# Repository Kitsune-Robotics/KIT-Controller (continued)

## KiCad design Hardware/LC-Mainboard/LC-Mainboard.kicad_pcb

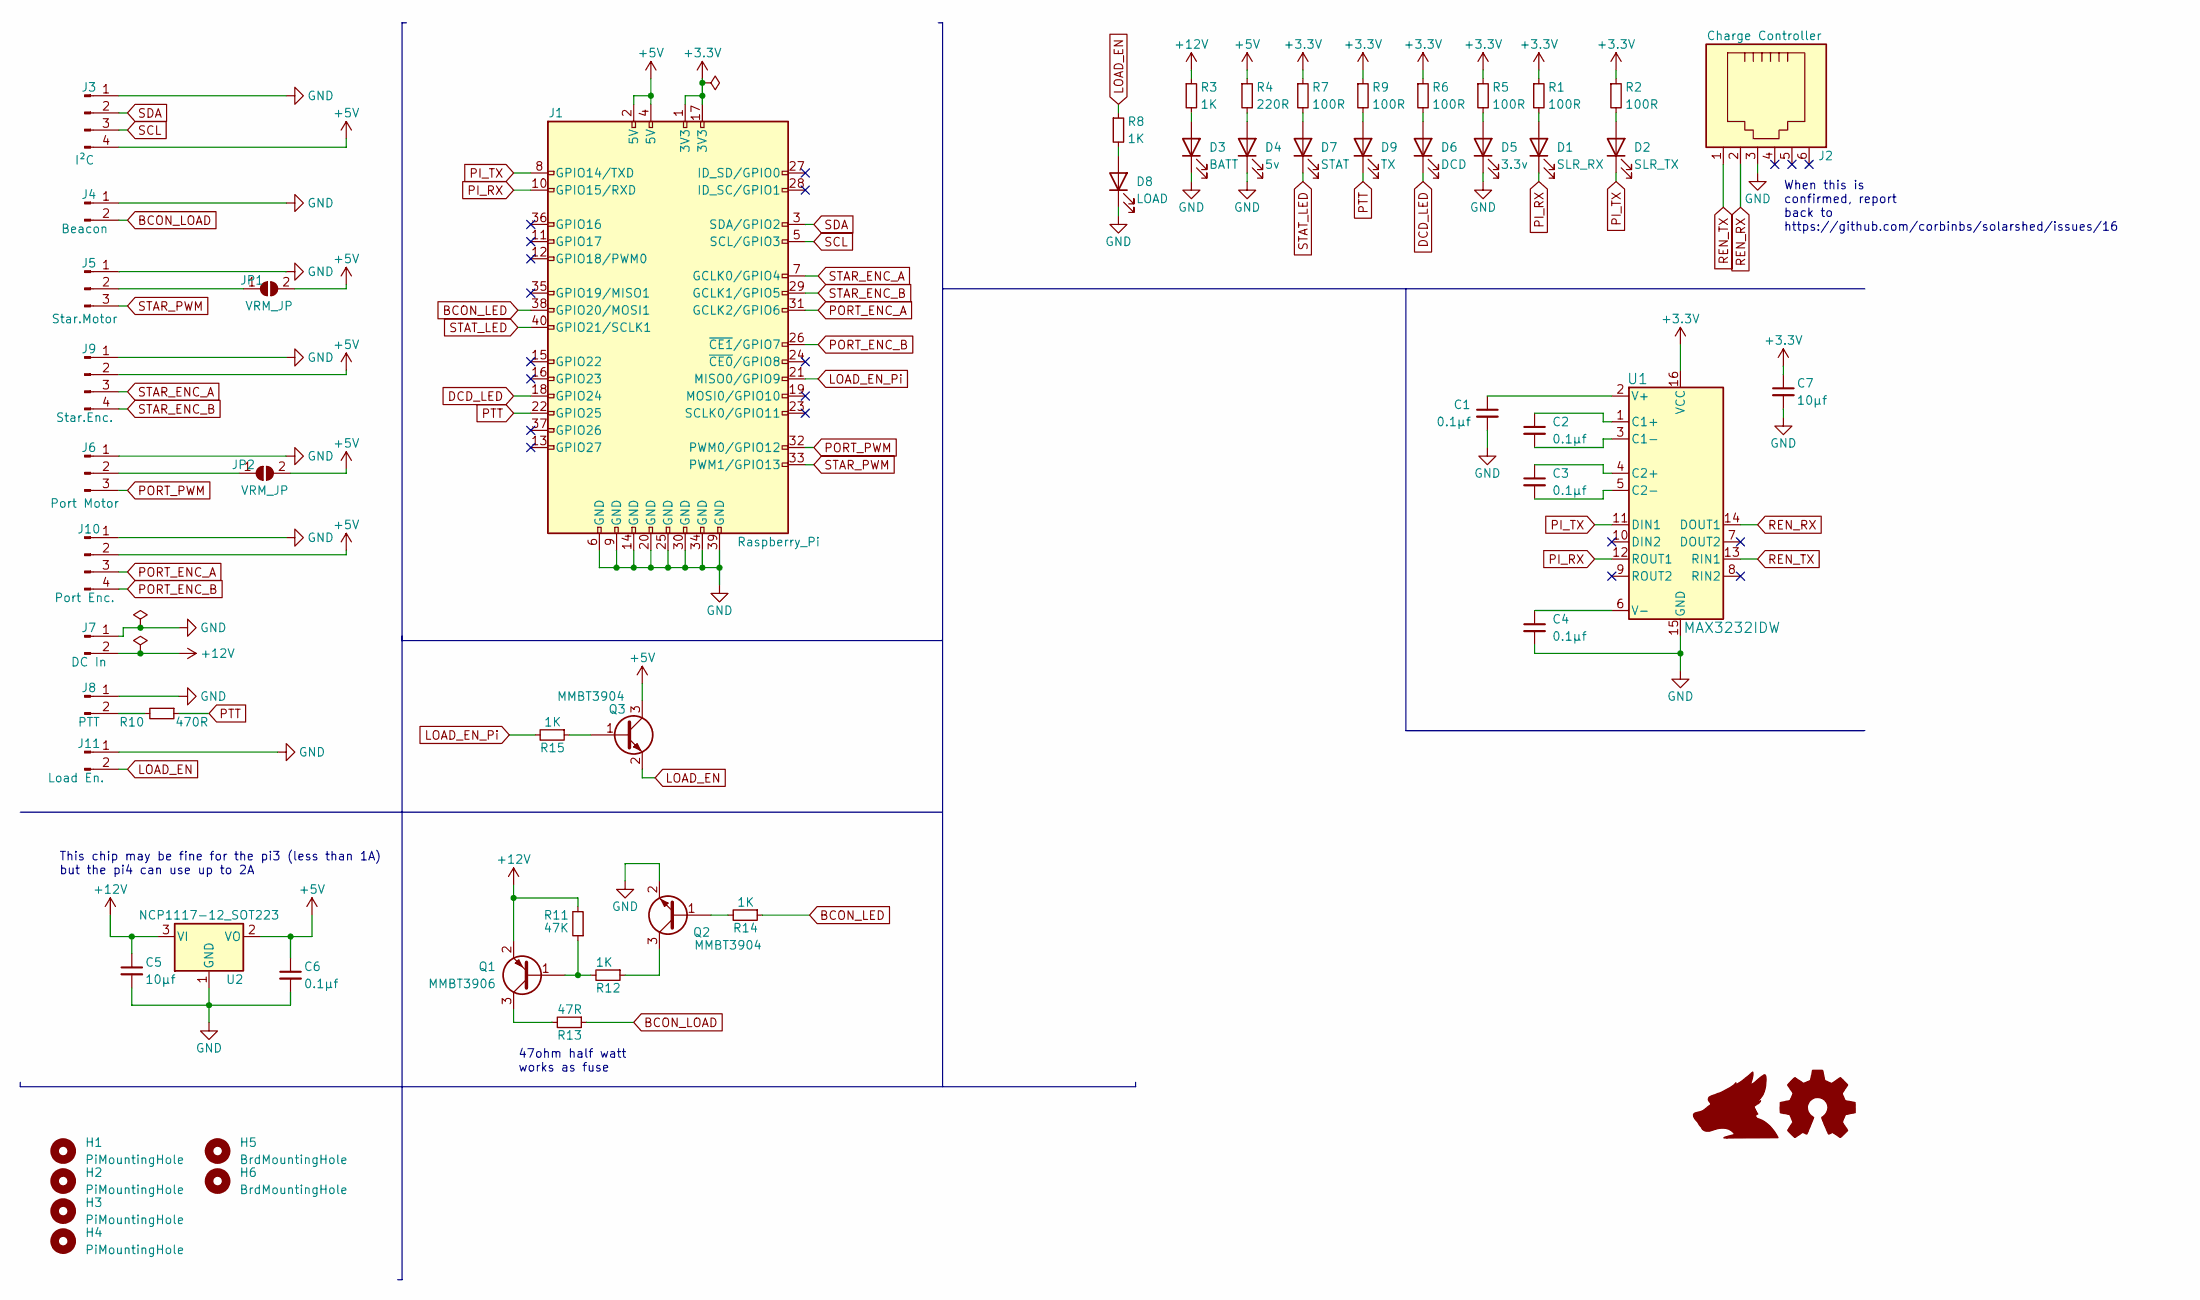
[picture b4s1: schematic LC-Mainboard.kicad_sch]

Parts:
C1, C2, C3, C4, C6: 0.1μf; C_0805_2012Metric
C5, C7: 10μf; C_Elec_4x5.4
D1: SLR_RX; LED_0805_2012Metric
D2: SLR_TX; LED_0805_2012Metric
D3: BATT; LED_0805_2012Metric
D4: 5v; LED_0805_2012Metric
D5: 3.3v; LED_0805_2012Metric
D6: DCD; LED_0805_2012Metric
D7: STAT; LED_0805_2012Metric
D8: LOAD; LED_0805_2012Metric
D9: TX; LED_0805_2012Metric
H1, H2, H3, H4: PiMountingHole; MountingHole_3mm
H5, H6: BrdMountingHole; MountingHole_3mm
J1: Raspberry_Pi; PinSocket_2x20_P2.54mm_Vertical
J2: Charge Controller; RJ12_Amphenol_54601
J3: I²C; JST_XH_S4B-XH-A_1x04_P2.50mm_Horizontal
J4: Beacon; JST_XH_S2B-XH-A_1x02_P2.50mm_Horizontal
J5: Star.Motor; JST_XH_S3B-XH-A_1x03_P2.50mm_Horizontal
J6: Port Motor; JST_XH_S3B-XH-A_1x03_P2.50mm_Horizontal
J7: DC In; JST_XH_S2B-XH-A_1x02_P2.50mm_Horizontal
J8: PTT; JST_XH_S2B-XH-A_1x02_P2.50mm_Horizontal
J9: Star.Enc.; JST_XH_S4B-XH-A_1x04_P2.50mm_Horizontal
J10: Port Enc.; JST_XH_S4B-XH-A_1x04_P2.50mm_Horizontal
J11: Load En.; JST_XH_S2B-XH-A_1x02_P2.50mm_Horizontal
JP1, JP2: VRM_JP; SolderJumper-2_P1.3mm_Open_Pad1.0x1.5mm
Q1: MMBT3906; SOT-23
Q2, Q3: MMBT3904; SOT-23
R1, R2, R5, R6, R7, R9: 100R; R_0805_2012Metric
R3, R8, R12, R14, R15: 1K; R_0805_2012Metric
R4: 220R; R_0805_2012Metric
R10: 470R; R_0805_2012Metric
R11: 47K; R_0805_2012Metric
R13: 47R; R_0805_2012Metric
U1: MAX3232IDW
U2: NCP1117-12_SOT223; SOT-223-3_TabPin2

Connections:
+3V3: C7.1, J1.1 (3V3), J1.17 (3V3), R1.1, R2.1, R5.1, R6.1, R7.1, R9.1, U1.16 (VCC)
+5V: C6.1, J1.2 (5V), J1.4 (5V), J3.4, J9.2, J10.2, JP1.2 (B), JP2.2 (B), Q3.3 (C), R4.1, U2.2 (VO)
+12V: C5.1, J7.2, Q1.2 (E), R3.1, R11.2, U2.3 (VI)
BCON_LED: J1.38 (GPIO20/MOSI1), R14.1
BCON_LOAD: J4.2, R13.1
DCD_LED: D6.1 (K), J1.18 (GPIO24)
GND: C1.2, C4.2, C5.2, C6.2, C7.2, D3.1 (K), D4.1 (K), D5.1 (K), D8.1 (K), J1.6 (GND), J1.9 (GND), J1.14 (GND), J1.20 (GND), J1.25 (GND), J1.30 (GND), J1.34 (GND), J1.39 (GND), J2.3, J3.1, J4.1, J5.1, J6.1, J7.1, J8.1, J9.1, J10.1, J11.1, Q2.2 (E), U1.15 (GND), U2.1 (GND)
LOAD_EN: J11.2, Q3.2 (E), R8.1
LOAD_EN_Pi: J1.21 (MISO0/GPIO9), R15.2
unnamed: C1.1, U1.2 (V+)
unnamed: C2.1, U1.1 (C1+)
unnamed: C2.2, U1.3 (C1-)
unnamed: C3.1, U1.4 (C2+)
unnamed: C3.2, U1.5 (C2-)
unnamed: C4.1, U1.6 (V-)
unnamed: D1.2 (A), R1.2
unnamed: D2.2 (A), R2.2
unnamed: D3.2 (A), R3.2
unnamed: D4.2 (A), R4.2
unnamed: D5.2 (A), R5.2
unnamed: D6.2 (A), R6.2
unnamed: D7.2 (A), R7.2
unnamed: D8.2 (A), R8.2
unnamed: D9.2 (A), R9.2
unnamed: J5.2, JP1.1 (A)
unnamed: J6.2, JP2.1 (A)
unnamed: J8.2, R10.2
unnamed: Q1.1 (B), R11.1, R12.2
unnamed: Q1.3 (C), R13.2
unnamed: Q2.1 (B), R14.2
unnamed: Q2.3 (C), R12.1
unnamed: Q3.1 (B), R15.1
PI_RX: D1.1 (K), J1.10 (GPIO15/RXD), U1.12 (ROUT1)
PI_TX: D2.1 (K), J1.8 (GPIO14/TXD), U1.11 (DIN1)
PORT_ENC_A: J1.31 (GCLK2/GPIO6), J10.3
PORT_ENC_B: J1.26 (~CE1/GPIO7), J10.4
PORT_PWM: J1.32 (PWM0/GPIO12), J6.3
PTT: D9.1 (K), J1.22 (GPIO25), R10.1
REN_RX: J2.2, U1.14 (DOUT1)
REN_TX: J2.1, U1.13 (RIN1)
SCL: J1.5 (SCL/GPIO3), J3.3
SDA: J1.3 (SDA/GPIO2), J3.2
STAR_ENC_A: J1.7 (GCLK0/GPIO4), J9.3
STAR_ENC_B: J1.29 (GCLK1/GPIO5), J9.4
STAR_PWM: J1.33 (PWM1/GPIO13), J5.3
STAT_LED: D7.1 (K), J1.40 (GPIO21/SCLK1)

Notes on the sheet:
When this is confirmed, report back to https://github.com/corbinbs/solarshed/issues/16
47ohm half watt works as fuse
This chip may be fine for the pi3 (less than 1A) but the pi4 can use up to 2A

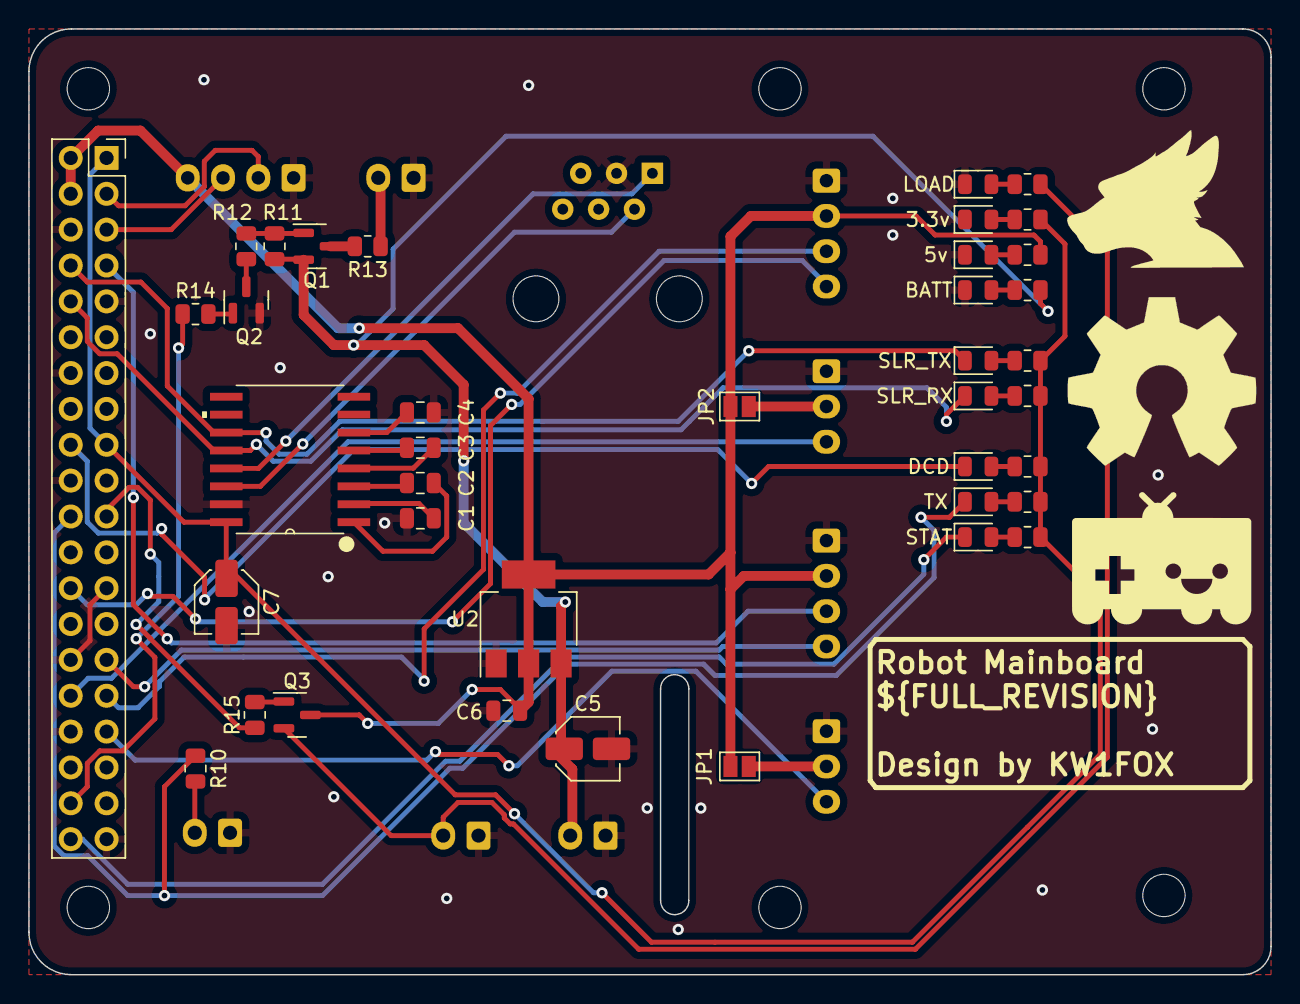
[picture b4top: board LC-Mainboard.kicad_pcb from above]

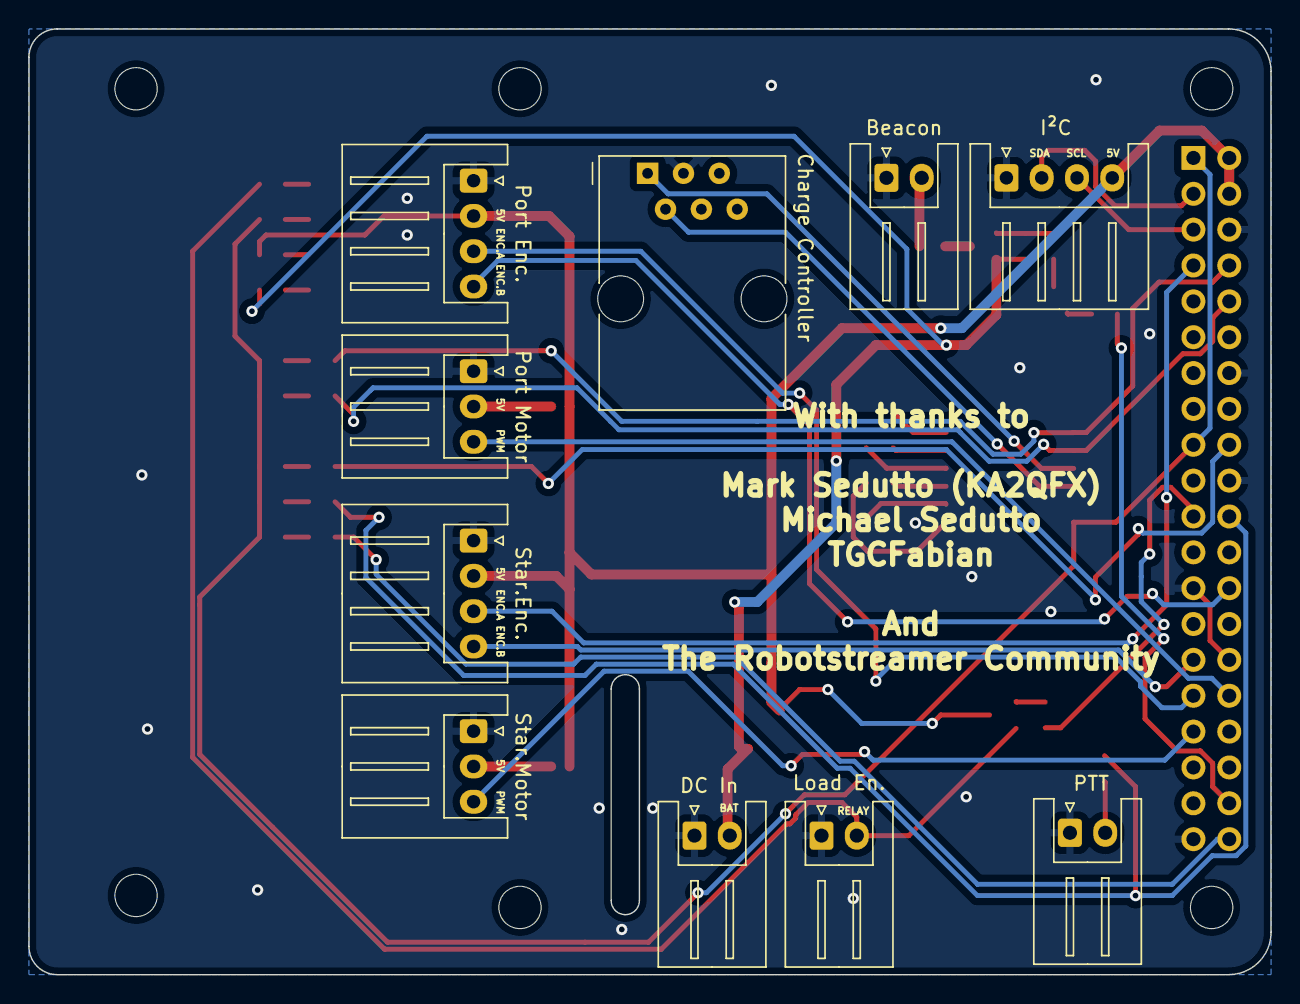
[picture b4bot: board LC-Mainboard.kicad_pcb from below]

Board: 2 copper layers, 88.0 x 67.0 mm, 55 parts (10 on the bottom side), 46 nets.

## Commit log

2022-04-12 import from feat/motor_mounts
2022-04-22 Bump CAD
2022-04-28 move everything
2022-04-28 Fixup new everything
2022-04-28 make encoder holder
2022-04-28 Clean encoder holder
2022-04-29 Fixup cad and assy
2022-04-29 Boilerplate PCB sketch
2022-04-29 Add lib depend, remove bak and boilerplate
2022-04-29 Update all
2022-04-29 Fix encoder spacer, bump lib and implement max3232 in sch
2022-04-29 Bump
2022-04-29 Init to commit it
2022-04-29 fixup! Init to commit it
2022-04-29 Bump logo
2022-04-29 Add designators
2022-04-30 bump lib and add LEDs
2022-04-30 Add a bunch of stuff
2022-04-30 Crawler Hardware (#1)
    This boilerplates all the hardware, a new branch should be made for producing a v0.1
2022-04-30 Switch to the correct connectors
2022-05-01 Do a little math
    Co-Authored by: Libidja
2022-05-01 Rearrange holes
2022-05-01 fixup! Rearrange holes
2022-05-03 Most of the routing is patched up, review with dad!
2022-05-03 Shrink board size
2022-05-03 Shrink board size even more!
2022-05-03 Add all wiring
2022-05-04 Add almost everything
2022-05-04 Add some extra things
2022-05-04 Fix 3d model
2022-05-04 Ready for review
2022-05-04 Add silkscreen
2022-05-04 Review from @ka2qfx went well!
2022-05-04 fixup! Review from @ka2qfx went well!
2022-05-04 Add last touches and fix all DRC
2022-05-04 fixup! Add last touches and fix all DRC
2022-05-04 Change direction, pi can now control load control
2022-05-04 Its done, all systems checked and final
2022-05-04 Make a v1.0 hardware release (#2)
2022-05-04 Add blank text variabes
2022-05-04 Add blank text variabes (#3)
    Seems to work fine and dosent interfere with text replacmeent in ci, merging.
2022-05-05 Update master assy
2022-05-05 Import v0.1 mainboard
2022-05-05 Only run on hardware paths
2022-05-09 Bump kicad libs
2022-05-19 Bump kicad
2022-05-19 Create inital Mastcam base
2022-05-19 Experiment with a new encoder base
    Suggestions by @ka2qfx
2022-05-19 Cleanup
2022-05-19 Fix bug rebuilding hardware on pull request
2022-05-19 resize encoder base
2022-05-19 Redesign mastcam base
2022-05-19 Add weighted wiper and 9g servo
2022-05-20 Fixup encoder and mastcam base
2022-05-21 Issue with smbus, fix l8r goodnight
2022-05-21 Move rospackages to the right location
2022-05-21 Create working inital LCD subscriber
2022-05-21 Halfway to a new package
2022-05-21 Got this working
2022-05-21 Add publisher
2022-05-21 Boilerplate pubsub
2022-05-21 Redo tutorial package live on stream
2022-05-21 Dont build on nothing
2022-05-21 Create a launchfile
2022-05-21 Add launch to make
2022-05-22 Cleanup names and add ros_workflow
2022-05-22 Fixup black formatting errors
2022-05-22 Update hardware_workflow.yml
    Fix a bug where workflow builds all the time evern when not needed
2022-05-22 Clean custom interfaces
2022-05-22 Custom message types!
2022-05-22 Handle multiple stats and cycle through them
2022-05-22 Add ci for ros2 lcd_viewer package
2022-05-22 Tests are dumb anyway
2022-05-22 Add all new mast parts
2022-05-22 Replace old mast parts with new ones
2022-05-22 Add new fancy feature EXPERIMENTAL
2022-05-23 Add small lip around base of camera pod drive gear
2022-05-23 Fix hole size on gearbox mounting plate
2022-05-23 Increase motor mounting bearing tolerence
2022-05-23 All done for the day
2022-05-23 Modify stuff idk i cant keep track of binary diffs
2022-05-23 Add top of box
2022-05-23 Clean up mastpod top
2022-05-24 Add camera housing base
2022-05-25 Add bottom mounting and sealing to pod housing
2022-05-25 Add mast pod base inital
2022-05-25 Add base to model
2022-05-25 Add more mounting holes and fluff
2022-05-25 More done to the top half
2022-05-25 Add limit switch
2022-05-26 Add sensors to mastcam base
2022-05-26 Create jig for solder mask
2022-05-26 Add cm4 template
2022-05-26 Add footprints too
2022-05-27 Add nokia libs
2022-05-27 Add encoder to drive gear
2022-05-27 Revert MastPodTop
2022-05-27 Extend pod height for potentometer
2022-05-27 Integrate encoder back into design
2022-05-27 Create glass and shell, more work needed
2022-05-27 Hide datum
2022-05-28 Improve fit
2022-06-09 Firmware doots
2022-06-09 Fix bug where PR would bypass checking if hardware needed to be built
2022-06-09 Create firmware workflow
2022-06-09 fixup! Create firmware workflow
2022-06-09 Change artifacts name
2022-06-09 Add cutout for 10 turn pot
2022-06-10 Fix serial debugging issue, thanks to Jck_true on IRC
2022-06-23 Replace caps with the right sized ones
2022-06-27 This doesent work
2022-06-30 Idk firmware
2022-10-01 clean modules
2022-10-02 bump lib with new backplane shared
2022-12-07 Inital migration of new kicad board
2022-12-07 Misc cleanup in .pro
2022-12-07 Satisfy constraints
2022-12-07 fixup! Satisfy constraints
2022-12-07 Fixup fixups and fixup the fixups
2022-12-08 Cleanup external libs and add extra bits to brd
2022-12-08 Pad more components
2022-12-08 Move MCU to its own schem
2022-12-08 add other junk idk
2022-12-08 Add more stuff
2022-12-08 Fixup drc
2022-12-10 Add short range modem
2022-12-20 Add TM1000 Tip over sensor and updates from custom lib
2022-12-20 Add clearance cutput in gearbox-mount
2023-02-08 Add inital glass
2023-07-10 bump all
2023-07-10 bump libs and squeeze into shape
2023-07-11 Add gnd and cleanup
2023-07-11 Add SD cardg
2023-07-13 include upstream fixes in kit controller
2023-10-23 Add stuff
2023-10-23 Not exactly the direction i want but, its a start
2023-10-23 Bump to new ver
2023-10-24 Remove software
2023-10-24 Add new pico firmware, depend on wizo libs
2023-10-24 Consider build flags later
2023-11-27 Add default freertosconfig
2023-11-27 Add default vfs config
2023-11-27 Add example includes from https://github.com/maxgerhardt/wizio-pico/blob/main/examples/picosdk-littlefs-freertos/src/main.cpp
2023-11-27 Add readme
2024-01-17 Add new base for future pieces
2024-01-22 Move CAD, make new sheet metal bend
2024-02-02 really want to print this
2024-04-02 Bump to kicad8
2024-04-02 Bump to kicad8 (again)
2024-04-02 Remove all CAD
2024-04-02 Remove simulation
2024-04-02 Clean all
2024-04-02 Everything New (#8)
2024-04-03 Import backplane from fennec modem
2024-04-03 Add libraries for backplane
2024-04-03 Bump to fix broken reference
2024-04-03 Bump backplane
2024-04-03 Remove bad ref**
2024-04-04 Include dev card
2024-04-04 Fix module bug
2024-04-04 Fix broken references
2024-04-04 Fix minor silkscreen bug
2024-04-04 Fix matrix
2024-04-05 Pivot to feather design
2024-04-05 Bump readme
2024-04-05 Few fixups on the dev card
2024-04-05 Prep for backplane proto
2024-04-05 So near to a backplane prototype now
2024-04-05 Remove broken refs
2024-04-05 Bump readme with instructions
2024-04-05 Plot footprint values for JLC export
2024-04-05 Hide hole ref
2024-04-05 Bump libs and docs
2024-04-05 Fix broken link
2024-04-05 Bump rails
2024-04-10 Add a little more silk to the dev card
2024-04-10 Add even more silkscreen
2024-04-10 Dont build the kit controller for upcoming release
2024-04-10 v1.1 Prototype (#11)
2024-04-10 New branch for next board
2024-05-08 modified rails
2024-05-08 Include template project
2024-05-08 My first build
2024-05-08 readme
2024-05-08 builtinLED is 13 on dev board
2024-05-11 Bump pico_sdk_impot.cmake from upstream
2024-05-11 Add new workflow
2024-05-11 Bump src
2024-05-11 Bump actions
2024-05-22 Add radio bootloader as a submodule
2024-06-04 Thought it would be cool to convert to cpp, seems to have done no harm?
2024-06-04 Early prototype for usb_console, works pretty well :
2024-06-04 Break everything up (and prototype foxtool)
2024-06-04 Break parent console away from usb_console
2024-06-04 Tidy and rename
2024-06-04 Code instantly locks up when it tries to parse but.. other than that its pretty cool:
2024-06-04 Queue still has issues but its getting somewhere!
2024-07-30 Create new 3d model for the prototype fontplate
    It has some issues tho, hole dosnt line up. you had one job joe!
2024-09-03 New tools and firmware!
2024-09-03 usb_console works!
2024-09-03 Very good
2024-09-03 Everything good
2024-09-03 Very advacned led blinker
2024-09-03 Add MCP_CAN lib
2024-09-03 Fix git.h
2024-09-03 Fix typo
2024-09-13 Bump pico mcp lib and configure all
2024-09-17 Bump pcb and can_controller
2025-11-19 Backplane now calls UNUSED5 5v offically
